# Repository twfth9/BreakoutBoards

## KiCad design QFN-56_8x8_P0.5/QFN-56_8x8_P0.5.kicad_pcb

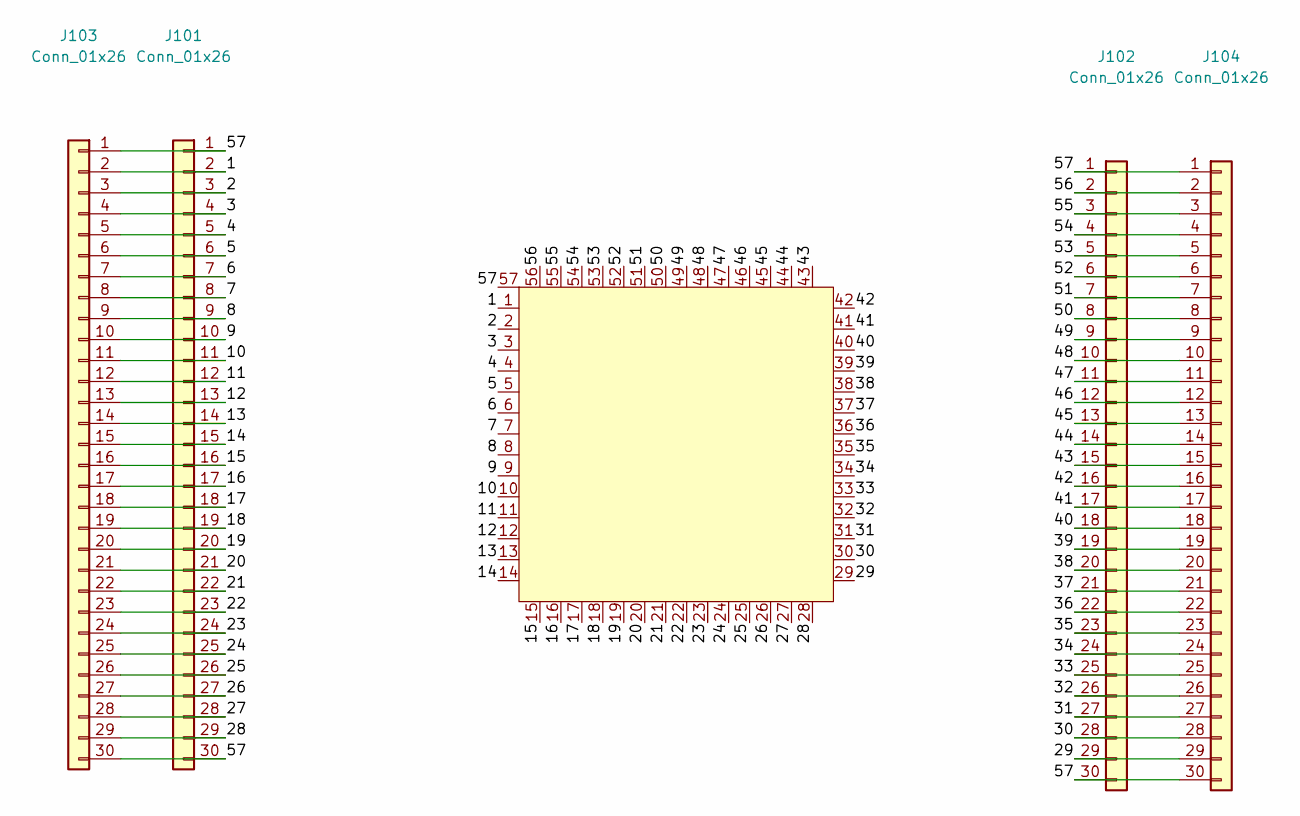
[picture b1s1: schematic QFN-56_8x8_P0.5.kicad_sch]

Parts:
J101, J102: Conn_01x26; PinHeader_1x30_P2.54mm_Vertical
J103: Conn_01x26; PinHeader_1x30_P2.54mm_Vertical_SMD_Pin1Left
J104: Conn_01x26; PinHeader_1x30_P2.54mm_Vertical_SMD_Pin1Right
U101: QFN-48; QFN-56-1EP_8x8mm_P0.5mm_EP4.3x4.3mm_ThermalVias

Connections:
/1: J101.2, J103.2, U101.1
/2: J101.3, J103.3, U101.2
/3: J101.4, J103.4, U101.3
/4: J101.5, J103.5, U101.4
/5: J101.6, J103.6, U101.5
/6: J101.7, J103.7, U101.6
/7: J101.8, J103.8, U101.7
/8: J101.9, J103.9, U101.8
/9: J101.10, J103.10, U101.9
/10: J101.11, J103.11, U101.10
/11: J101.12, J103.12, U101.11
/12: J101.13, J103.13, U101.12
/13: J101.14, J103.14, U101.13
/14: J101.15, J103.15, U101.14
/15: J101.16, J103.16, U101.15
/16: J101.17, J103.17, U101.16
/17: J101.18, J103.18, U101.17
/18: J101.19, J103.19, U101.18
/19: J101.20, J103.20, U101.19
/20: J101.21, J103.21, U101.20
/21: J101.22, J103.22, U101.21
/22: J101.23, J103.23, U101.22
/23: J101.24, J103.24, U101.23
/24: J101.25, J103.25, U101.24
/25: J101.26, J103.26, U101.25
/26: J101.27, J103.27, U101.26
/27: J101.28, J103.28, U101.27
/28: J101.29, J103.29, U101.28
/29: J102.29, J104.29, U101.29
/30: J102.28, J104.28, U101.30
/31: J102.27, J104.27, U101.31
/32: J102.26, J104.26, U101.32
/33: J102.25, J104.25, U101.33
/34: J102.24, J104.24, U101.34
/35: J102.23, J104.23, U101.35
/36: J102.22, J104.22, U101.36
/37: J102.21, J104.21, U101.37
/38: J102.20, J104.20, U101.38
/39: J102.19, J104.19, U101.39
/40: J102.18, J104.18, U101.40
/41: J102.17, J104.17, U101.41
/42: J102.16, J104.16, U101.42
/43: J102.15, J104.15, U101.43
/44: J102.14, J104.14, U101.44
/45: J102.13, J104.13, U101.45
/46: J102.12, J104.12, U101.46
/47: J102.11, J104.11, U101.47
/48: J102.10, J104.10, U101.48
/49: J102.9, J104.9, U101.49
/50: J102.8, J104.8, U101.50
/51: J102.7, J104.7, U101.51
/52: J102.6, J104.6, U101.52
/53: J102.5, J104.5, U101.53
/54: J102.4, J104.4, U101.54
/55: J102.3, J104.3, U101.55
/56: J102.2, J104.2, U101.56
/57: J101.1, J101.30, J102.1, J102.30, J103.1, J103.30, J104.1, J104.30, U101.57

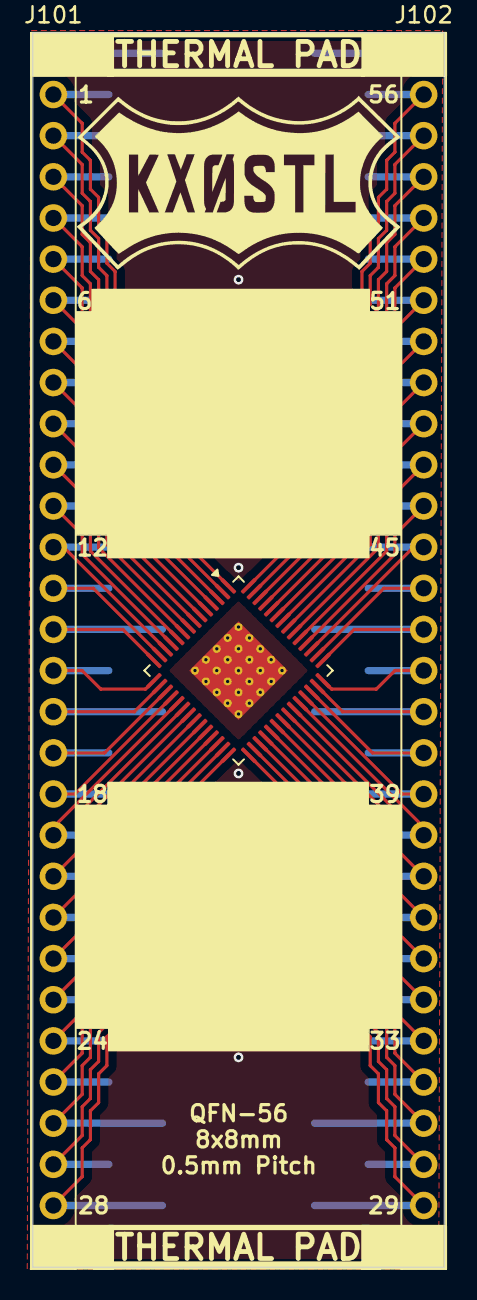
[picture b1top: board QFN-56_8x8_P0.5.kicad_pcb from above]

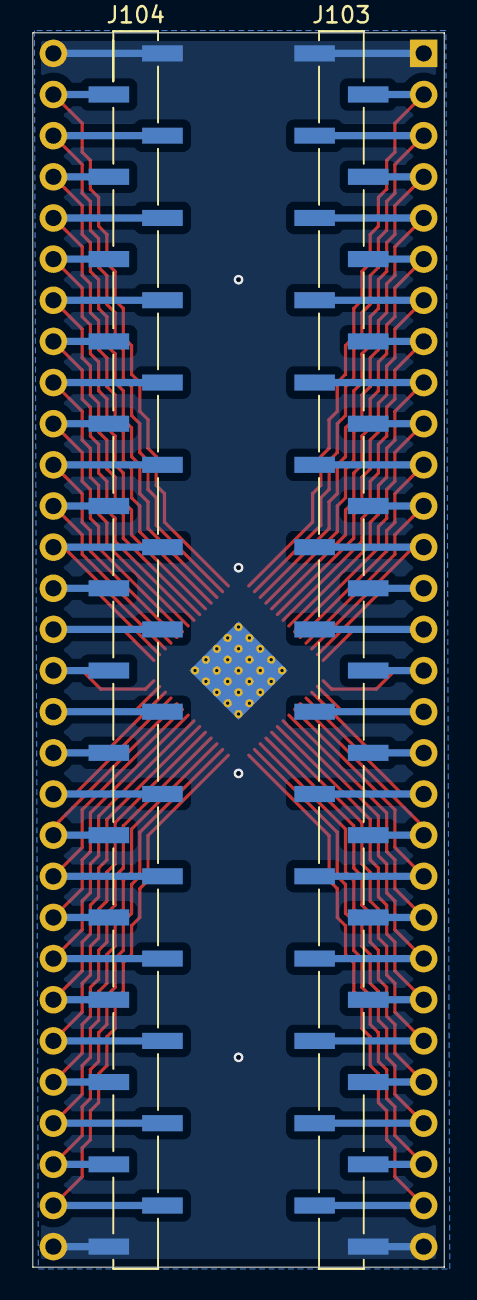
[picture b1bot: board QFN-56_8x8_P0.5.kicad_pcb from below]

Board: 2 copper layers, 25.4 x 76.2 mm, 5 parts (2 on the bottom side), 57 nets.

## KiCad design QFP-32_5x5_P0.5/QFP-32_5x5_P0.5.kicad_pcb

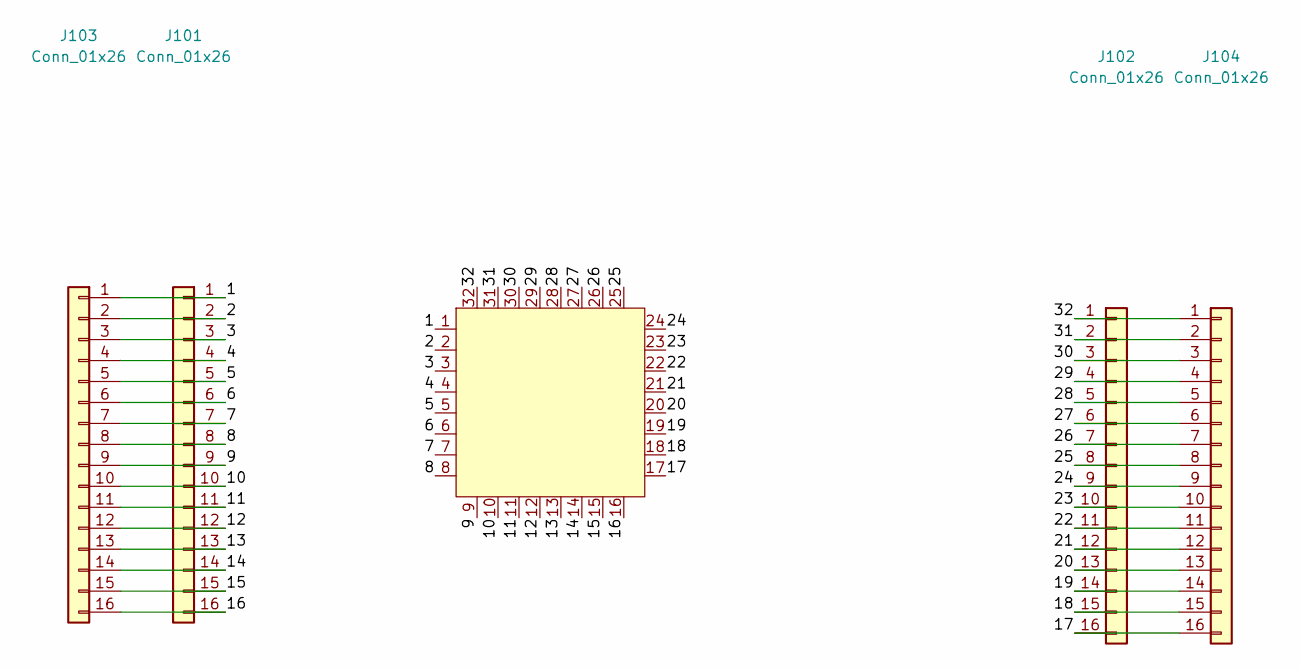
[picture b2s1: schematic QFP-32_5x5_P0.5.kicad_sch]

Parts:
J101, J102: Conn_01x26; PinHeader_1x16_P2.54mm_Vertical
J103: Conn_01x26; PinHeader_1x16_P2.54mm_Vertical_SMD_Pin1Left
J104: Conn_01x26; PinHeader_1x16_P2.54mm_Vertical_SMD_Pin1Right
U101: QFN-48; TQFP-32_5x5mm_P0.5mm

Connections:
/1: J101.1, J103.1, U101.1
/2: J101.2, J103.2, U101.2
/3: J101.3, J103.3, U101.3
/4: J101.4, J103.4, U101.4
/5: J101.5, J103.5, U101.5
/6: J101.6, J103.6, U101.6
/7: J101.7, J103.7, U101.7
/8: J101.8, J103.8, U101.8
/9: J101.9, J103.9, U101.9
/10: J101.10, J103.10, U101.10
/11: J101.11, J103.11, U101.11
/12: J101.12, J103.12, U101.12
/13: J101.13, J103.13, U101.13
/14: J101.14, J103.14, U101.14
/15: J101.15, J103.15, U101.15
/16: J101.16, J103.16, U101.16
/17: J102.16, J104.16, U101.17
/18: J102.15, J104.15, U101.18
/19: J102.14, J104.14, U101.19
/20: J102.13, J104.13, U101.20
/21: J102.12, J104.12, U101.21
/22: J102.11, J104.11, U101.22
/23: J102.10, J104.10, U101.23
/24: J102.9, J104.9, U101.24
/25: J102.8, J104.8, U101.25
/26: J102.7, J104.7, U101.26
/27: J102.6, J104.6, U101.27
/28: J102.5, J104.5, U101.28
/29: J102.4, J104.4, U101.29
/30: J102.3, J104.3, U101.30
/31: J102.2, J104.2, U101.31
/32: J102.1, J104.1, U101.32

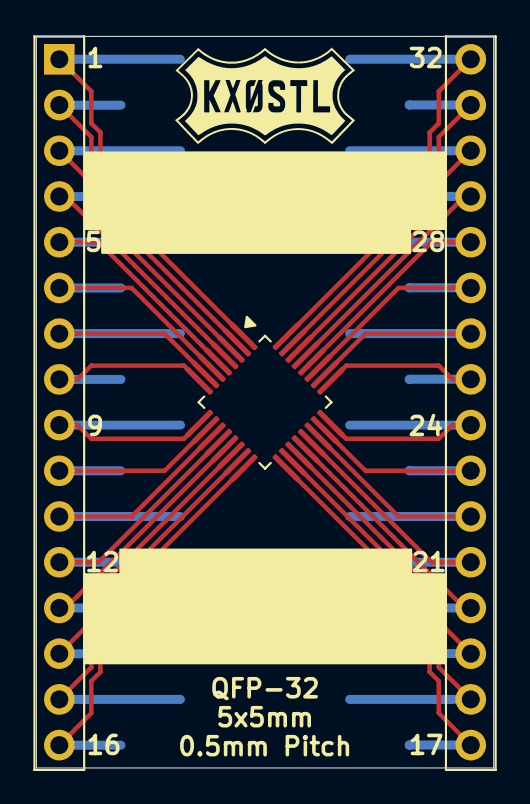
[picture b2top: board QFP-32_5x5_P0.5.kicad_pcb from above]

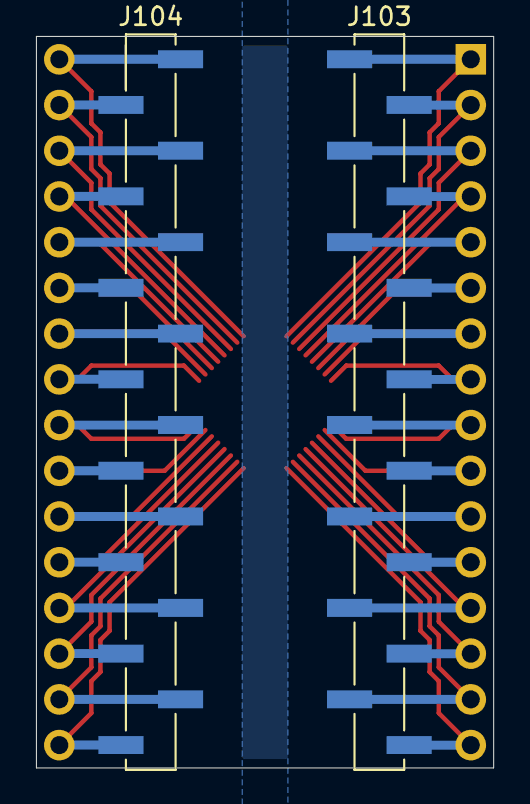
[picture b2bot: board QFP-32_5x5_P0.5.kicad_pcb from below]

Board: 2 copper layers, 25.4 x 40.6 mm, 5 parts (2 on the bottom side), 32 nets.

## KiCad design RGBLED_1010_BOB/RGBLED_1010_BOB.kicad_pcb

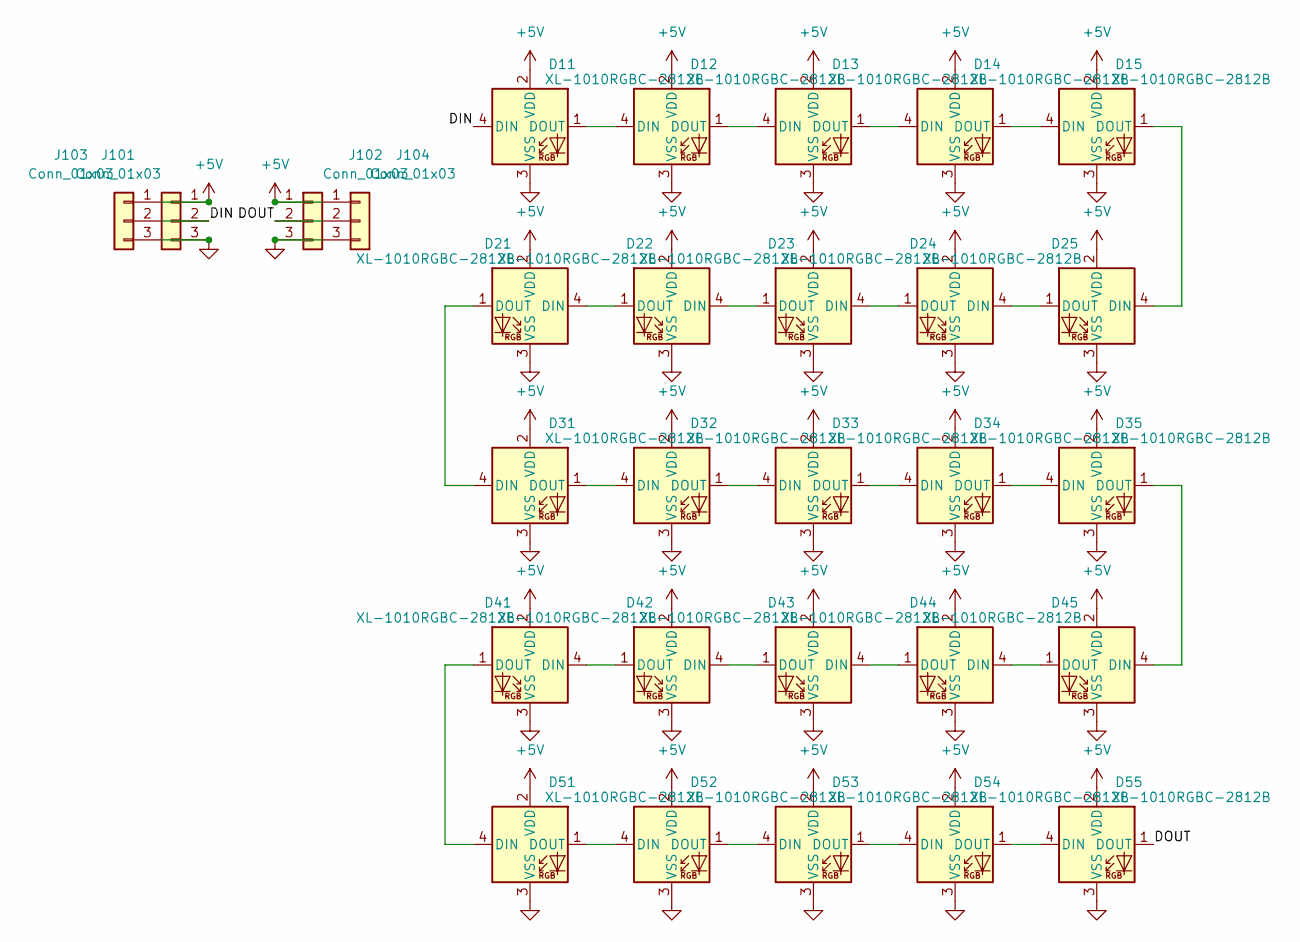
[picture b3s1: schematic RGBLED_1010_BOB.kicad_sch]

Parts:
D11, D12, D13, D14, D15, D21, D22, D23, D24, D25, D31, D32, D33, D34, D35, D41, D42, D43, D44, D45, D51, D52, D53, D54, D55: XL-1010RGBC-2812B
J101: Conn_01x03; PinHeader_1x03_P2.54mm_Vertical_SMD_Pin1Left
J102: Conn_01x03; PinHeader_1x03_P2.54mm_Vertical_SMD_Pin1Right
J103, J104: Conn_01x03; PinHeader_1x03_P2.54mm_Vertical

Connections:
+5V: D11.2 (VDD), D12.2 (VDD), D13.2 (VDD), D14.2 (VDD), D15.2 (VDD), D21.2 (VDD), D22.2 (VDD), D23.2 (VDD), D24.2 (VDD), D25.2 (VDD), D31.2 (VDD), D32.2 (VDD), D33.2 (VDD), D34.2 (VDD), D35.2 (VDD), D41.2 (VDD), D42.2 (VDD), D43.2 (VDD), D44.2 (VDD), D45.2 (VDD), D51.2 (VDD), D52.2 (VDD), D53.2 (VDD), D54.2 (VDD), D55.2 (VDD), J101.1, J102.1, J103.1, J104.1
/DIN: D11.4 (DIN), J101.2, J103.2
/DOUT: D55.1 (DOUT), J102.2, J104.2
GND: D11.3 (VSS), D12.3 (VSS), D13.3 (VSS), D14.3 (VSS), D15.3 (VSS), D21.3 (VSS), D22.3 (VSS), D23.3 (VSS), D24.3 (VSS), D25.3 (VSS), D31.3 (VSS), D32.3 (VSS), D33.3 (VSS), D34.3 (VSS), D35.3 (VSS), D41.3 (VSS), D42.3 (VSS), D43.3 (VSS), D44.3 (VSS), D45.3 (VSS), D51.3 (VSS), D52.3 (VSS), D53.3 (VSS), D54.3 (VSS), D55.3 (VSS), J101.3, J102.3, J103.3, J104.3
unnamed: D11.1 (DOUT), D12.4 (DIN)
unnamed: D12.1 (DOUT), D13.4 (DIN)
unnamed: D13.1 (DOUT), D14.4 (DIN)
unnamed: D14.1 (DOUT), D15.4 (DIN)
unnamed: D15.1 (DOUT), D25.4 (DIN)
unnamed: D21.4 (DIN), D22.1 (DOUT)
unnamed: D21.1 (DOUT), D31.4 (DIN)
unnamed: D22.4 (DIN), D23.1 (DOUT)
unnamed: D23.4 (DIN), D24.1 (DOUT)
unnamed: D24.4 (DIN), D25.1 (DOUT)
unnamed: D31.1 (DOUT), D32.4 (DIN)
unnamed: D32.1 (DOUT), D33.4 (DIN)
unnamed: D33.1 (DOUT), D34.4 (DIN)
unnamed: D34.1 (DOUT), D35.4 (DIN)
unnamed: D35.1 (DOUT), D45.4 (DIN)
unnamed: D41.4 (DIN), D42.1 (DOUT)
unnamed: D41.1 (DOUT), D51.4 (DIN)
unnamed: D42.4 (DIN), D43.1 (DOUT)
unnamed: D43.4 (DIN), D44.1 (DOUT)
unnamed: D44.4 (DIN), D45.1 (DOUT)
unnamed: D51.1 (DOUT), D52.4 (DIN)
unnamed: D52.1 (DOUT), D53.4 (DIN)
unnamed: D53.1 (DOUT), D54.4 (DIN)
unnamed: D54.1 (DOUT), D55.4 (DIN)

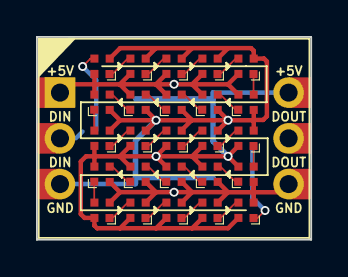
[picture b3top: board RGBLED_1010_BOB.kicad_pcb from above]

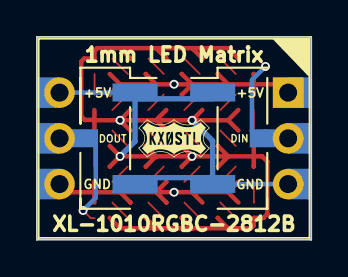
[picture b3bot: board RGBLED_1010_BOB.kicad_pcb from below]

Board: 2 copper layers, 15.2 x 11.3 mm, 29 parts (2 on the bottom side), 28 nets.
